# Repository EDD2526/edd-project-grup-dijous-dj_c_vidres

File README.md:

View this project on [CADLAB.io](https://cadlab.io/project/30197).

# Projecte DJ_C_Vidres (Portes)

> **Autors: Gurpinder Singh Kaur, Adria Pelegri Sabate**  
> **Versió: 5**

---

## Objectiu

PCB per al control d’un sistema de porta i alçavidres d’un vehicle. La placa permet controlar el moviment del vidre i l’actuació de la porta mitjançant botons, gestionar motors amb drivers pont H, detectar finals de carrera i situacions de sobrecorrent, i comunicar-se amb altres sistemes del vehicle mitjançant CAN. També inclou mecanismes de protecció, regulació d’alimentació, programació/debug mitjançant ICSP i test points per facilitar la depuració.

---

## Diagrama de blocs

---

## Descripció funcional dels blocs

### Alimentació

La placa s’alimenta a partir d’una entrada de 12 V del vehicle. Aquesta entrada està protegida mitjançant fusible, díode de protecció i TVS. A partir d’aquesta tensió es genera una línia de 5 V mitjançant un convertidor DC-DC LM2596S-5.0. Posteriorment, es genera una línia de 3.3 V mitjançant un regulador LM1117-3.3 per alimentar la lògica digital, el microcontrolador, el transceptor CAN i els perifèrics de baixa tensió.

### Microcontrolador

El sistema està controlat per un microcontrolador **PIC24HJ128GP504-I/PT** alimentat a 3.3 V. Aquest dispositiu gestiona les entrades de botons i sensors, genera les ordres de control dels drivers de motor, llegeix el senyal analògic de corrent, comunica amb el lector RFID i permet la comunicació amb altres sistemes mitjançant CAN.

La placa inclou connector de programació/debug ICSP amb les línies MCLR, PGEC i PGED.

### Drivers de motor

S’utilitzen dos drivers **VNH5019A-E** en configuració de pont H:

- Un driver per al motor  de l’alçavidres;
- Un driver per al motor actuador de la porta.

Cada driver permet controlar el motor en ambdós sentits mitjançant senyals digitals INA, INB i PWM.

### Mesura de corrent i antiatrapament

La mesura de corrent es realitza mitjançant la sortida de current sense del driver VNH5019A-E. Aquest senyal s’envia a una entrada ADC del microcontrolador per detectar situacions de sobrecorrent. Aquesta informació permet implementar una funció  tipus antiatrapament en el motor de l’alçavidres.

### Inputs d’usuari i sensors

La placa incorpora entrades per a:

- Botons de pujada i baixada de l’alçavidres
- Control de bloqueig/desbloqueig de porta
- Sensor de final de carrera

Les entrades digitals es connecten al microcontrolador mitjançant resistències de pull-up/pull-down segons la funcionalitat requerida.

### RFID

El sistema inclou connexió per a un lector RFID RC522. Aquest mòdul permet identificar l’usuari o autoritzar accions del sistema. La comunicació amb el microcontrolador es realitza mitjançant SPI.

### Comunicació CAN

La comunicació amb altres sistemes del vehicle es realitza mitjançant un transceptor **SN65HVD230**. El bus CAN disposa de les línies CANH i CANL.

---

## Requisits / Especificacions

### Alimentació

- Entrada principal: 12 V
- Sortida intermèdia: 5 V
- Alimentació lògica: 3.3 V
- Protecció d’entrada mitjançant fusible, díode i TVS

### Microcontrolador

- Model: PIC24HJ128GP504-I/PT
- Encapsulat: TQFP-44
- Alimentació: 3.3 V
- Programació/debug: ICSP
- Perifèrics utilitzats:
  - PWM per al control dels motors
  - ADC per a la lectura de corrent
  - SPI per al lector RFID
  - CAN per a la comunicació amb el vehicle
  - GPIO per a botons, sensors i diagnòstic

### Motors

- Motor alçavidres:
  - Alimentació: 12 V
  - Corrent màxim estimat: fins a 3 A

- Motor actuador de porta:
  - Alimentació: 12 V
  - Control bidireccional mitjançant pont H
  - Control PWM

### Funcionalitats principals

- Control bidireccional dels motors
- Control de velocitat mitjançant PWM
- Lectura de botons d’usuari
- Lectura de final de carrera
- Detecció de sobrecorrent
- Diagnòstic dels drivers de motor
- Comunicació CAN
- Connexió RFID
- Programació i debug mitjançant ICSP
- Test point per depuració

---

## Components principals

| # | Component | Valor | Quantitat | Footprint | Preu x1 (€) |
|---|---|---|---|---|---|
| 1 | Capacitor | 100nF | 12 | Capacitor_SMD:C_0805_2012Metric | 0,09 |
| 2 | Capacitor | 10uF | 6 | Capacitor_SMD:C_0805_2012Metric | 0,79 |
| 3 | Capacitor | 220uF | 1 | Capacitor_SMD:CP_Elec_8x10 | 0,46 |
| 4 | Capacitor | 22pF | 2 | Capacitor_SMD:C_0805_2012Metric | 0,67 |
| 5 | Capacitor | 100uF | 1 | Capacitor_SMD:CP_Elec_8x10 | 0,69 |
| 6 | Diode Schottky | - | 2 | Diode_SMD:D_SMB_Modified | 0,22 |
| 7 | Diode TVS | - | 1 | Diode_SMD:D_SMB_Modified | 0,66 |
| 8 | Fuse | - | 1 | Fuse:Fuse_1812_4532Metric | 0,45 |
| 9 | Connector | - | 2 | Connector_Dsub:DSUB-9_Pins_Horizontal_P2.77x2.84mm_EdgePinOffset4.9 | 3,89 |
| 10 | Connector | - | 1 | Connector_PinSocket_1.00mm:PinSocket_1x08_P1.00mm_Vertical | 0,80 |
| 11 | Connector | - | 1 | Connector_PinHeader_2.54mm:PinHeader_1x05_P2.54mm_Vertical | 0,24 |
| 12 | Connector | - | 4 | TerminalBlock:TerminalBlock_MaiXu_MX126-5.0-02P_1x02_P5.00mm | 0,09 |
| 13 | Inductor | 33uH | 1 | Inductor_SMD:L_10.4x10.4_H4.8 | 1,38 |
| 14 | Resistor | 120Ω | 1 | Resistor_SMD:R_0805_2012Metric | 1,08 |
| 15 | Resistor | 10kΩ | 10 | Resistor_SMD:R_0805_2012Metric | 1,08 |
| 16 | Resistor | 1kΩ | 1 | Resistor_SMD:R_0805_2012Metric | 1,08 |
| 17 | Switch | - | 1 | Button_Switch_SMD:SW_DPDT_CK_JS202011JCQN | 0,86 |
| 18 | Switch | - | 1 | Button_Switch_THT:SW_CK_JS202011CQN_DPDT_Straight | 0,74 |
| 19 | Switch | - | 1 | Button_Switch_SMD:SW_SPST_TL3342 | 0,50 |
| 20 | Micro | - | 1 | PIC24HJ128GP504-I_PT:QFP80P1200X1200X120-44N | 7,23 |
| 21 | Transceiver | - | 1 | PACKAGE_SO:SOIC-8_3.9x4.9mm_P1.27mm | 1,87 |
| 22 | Motor Drivers | - | 2 | Package_SO:ST_MultiPowerSO-30 | 7,93 |
| 23 | DC-DC | - | 1 | Package_TO_SOT_SMD:TO-263-5_TabPin3 | 5,99 |
| 24 | DC-DC | - | 1 | Package_TO_SOT_SMD:TO-252-3_TabPin2 | 1,12 |
| 25 | Crystal | 8MHz | 1 | Crystal:Crystal_SMD_3225-4Pin_3.2x2.5mm | 0,53 |

## Disseny PCB

La PCB s’ha dissenyat a **dues capes**. S’ha intentat separar funcionalment la zona de potència i la zona lògica per reduir interferències i facilitar el routing.

### Criteris principals de disseny

- Zona de potència situada principalment a l’esquerra de la PCB.
- Microcontrolador situat a la zona central.
- Comunicacions CAN i connectors principals situats a la dreta.
- Inputs i botons situats a la zona inferior/superior.
- Pla de VBAT_PROT per alimentar els drivers de motor.
- Pla de +3.3V per alimentar la part digital.
- Separació entre GND i GNDPWR
- Pistes de potència més amples que les pistes de senyal.
- Test points  per a alimentació, debug, CAN, PWM, diagnòstic i corrent.

### Bus CAN

El transceptor CAN s’ha col·locat pròxim al connector corresponent. Les línies `CANH` i `CANL` s’han mantingut curtes i amb una disposició simètrica.

---

## Test points

S’han afegit test points per facilitar la posada en marxa i la depuració de la placa. Els punts principals són:

- TP_VBAT: alimentació protegida de 12 V
- TP_5V: sortida del convertidor DC-DC
- TP_3V3: alimentació lògica
- TP_GND: massa lògica
- TP_GNDPWR: massa de potència
- TP_MCLR: reset/programació
- TP_PGEC: línia de clock ICSP
- TP_PGED: línia de dades ICSP
- TP_CANH: línia CANH
- TP_CANL: línia CANL
- TP_CURRENT: lectura de corrent
- TP_PWM: control PWM
- TP_WDIAG: diagnòstic del driver de finestra
- TP_DDIAG: diagnòstic del driver de porta

Aquests punts permeten verificar alimentació, comunicació, programació, control dels motors i diagnòstic sense modificar la placa.

---

## Software

### Eines utilitzades

- KiCad 9.0
- LTspice per a simulacions

### Configuració prevista del microcontrolador

- PWM per al control dels drivers de motor
- ADC per a lectura del senyal de corrent
- SPI per al lector RFID
- CAN per a comunicació amb el vehicle
- GPIO per a botons, sensors, finals de carrera i diagnòstic
- ICSP per a programació i debug

### Funcionalitats previstes

#### Control de motors

- Control de pujada i baixada del vidre
- Control d’actuació de la porta
- Control de velocitat mitjançant PWM
- Control de sentit mitjançant INA i INB

#### Seguretat

- Detecció de sobrecorrent
- Funció antiatrapament
- Lectura de final de carrera
- Diagnòstic dels drivers de motor

#### Comunicació

- Comunicació CAN amb altres sistemes del vehicle
- Comunicació SPI amb el lector RFID

#### Debug

- Programació mitjançant ICSP
- Test points per a mesures elèctriques

---

## Verificació

Abans de la fabricació/entrega s’han revisat els punts següents:

- ERC del circuit esquemàtic:
  - 0 errors
  - 6 avisos 
- DRC de la PCB:
  - 0 errors
  - 0 avisos
- Separació entre zona de potència i zona lògica.
- Bus CAN curt i simètric.
- Serigrafia completa i llegible.
- Test points accessibles.

---

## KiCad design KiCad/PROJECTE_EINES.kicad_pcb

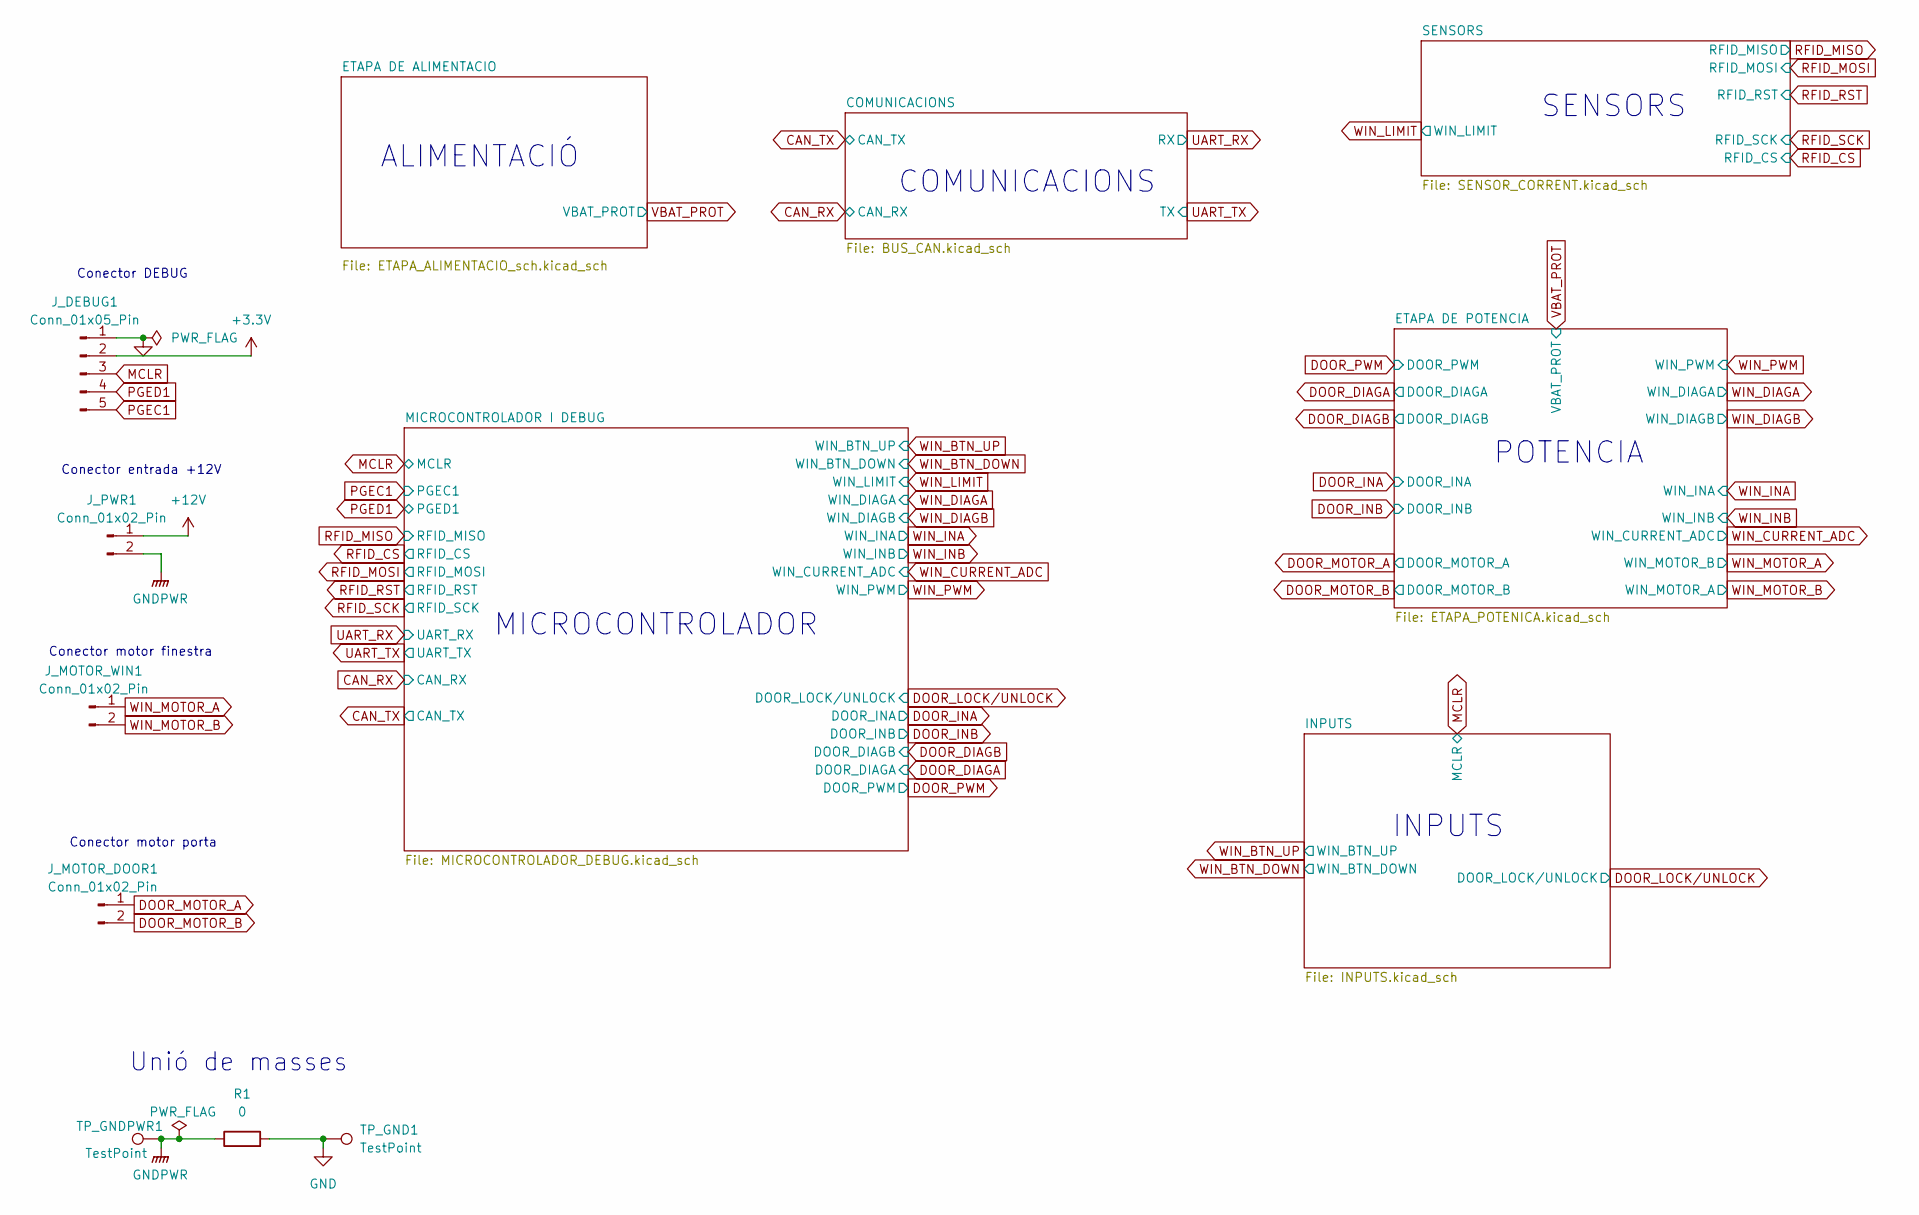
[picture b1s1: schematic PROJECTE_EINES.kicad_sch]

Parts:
J_DEBUG1: Conn_01x05_Pin; PinHeader_1x05_P2.54mm_Vertical
J_MOTOR_DOOR1: Conn_01x02_Pin; TerminalBlock_MaiXu_MX126-5.0-02P_1x02_P5.00mm
J_MOTOR_WIN1: Conn_01x02_Pin; TerminalBlock_MaiXu_MX126-5.0-02P_1x02_P5.00mm
J_PWR1: Conn_01x02_Pin; TerminalBlock_MaiXu_MX126-5.0-02P_1x02_P5.00mm
R1: 0; R_0805_2012Metric
TP_GND1: TestPoint; TestPoint_Pad_D1.5mm
TP_GNDPWR1: TestPoint; TestPoint_Pad_D1.5mm

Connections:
+3.3V: J_DEBUG1.2; also elsewhere on the board
+12V: J_PWR1.1; also elsewhere on the board
DOOR_MOTOR_A: J_MOTOR_DOOR1.1; also elsewhere on the board
DOOR_MOTOR_B: J_MOTOR_DOOR1.2; also elsewhere on the board
GND: J_DEBUG1.1, R1.2, TP_GND1.1; also elsewhere on the board
GNDPWR: J_PWR1.2, R1.1, TP_GNDPWR1.1; also elsewhere on the board
MCLR: J_DEBUG1.3; also elsewhere on the board
PGEC1: J_DEBUG1.5; also elsewhere on the board
PGED1: J_DEBUG1.4; also elsewhere on the board
WIN_MOTOR_A: J_MOTOR_WIN1.1; also elsewhere on the board
WIN_MOTOR_B: J_MOTOR_WIN1.2; also elsewhere on the board

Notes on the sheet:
Unió de masses
COMUNICACIONS
POTENCIA
Conector motor finestra
Conector DEBUG
MICROCONTROLADOR
INPUTS
Conector motor porta
ALIMENTACIÓ
Conector entrada +12V
SENSORS

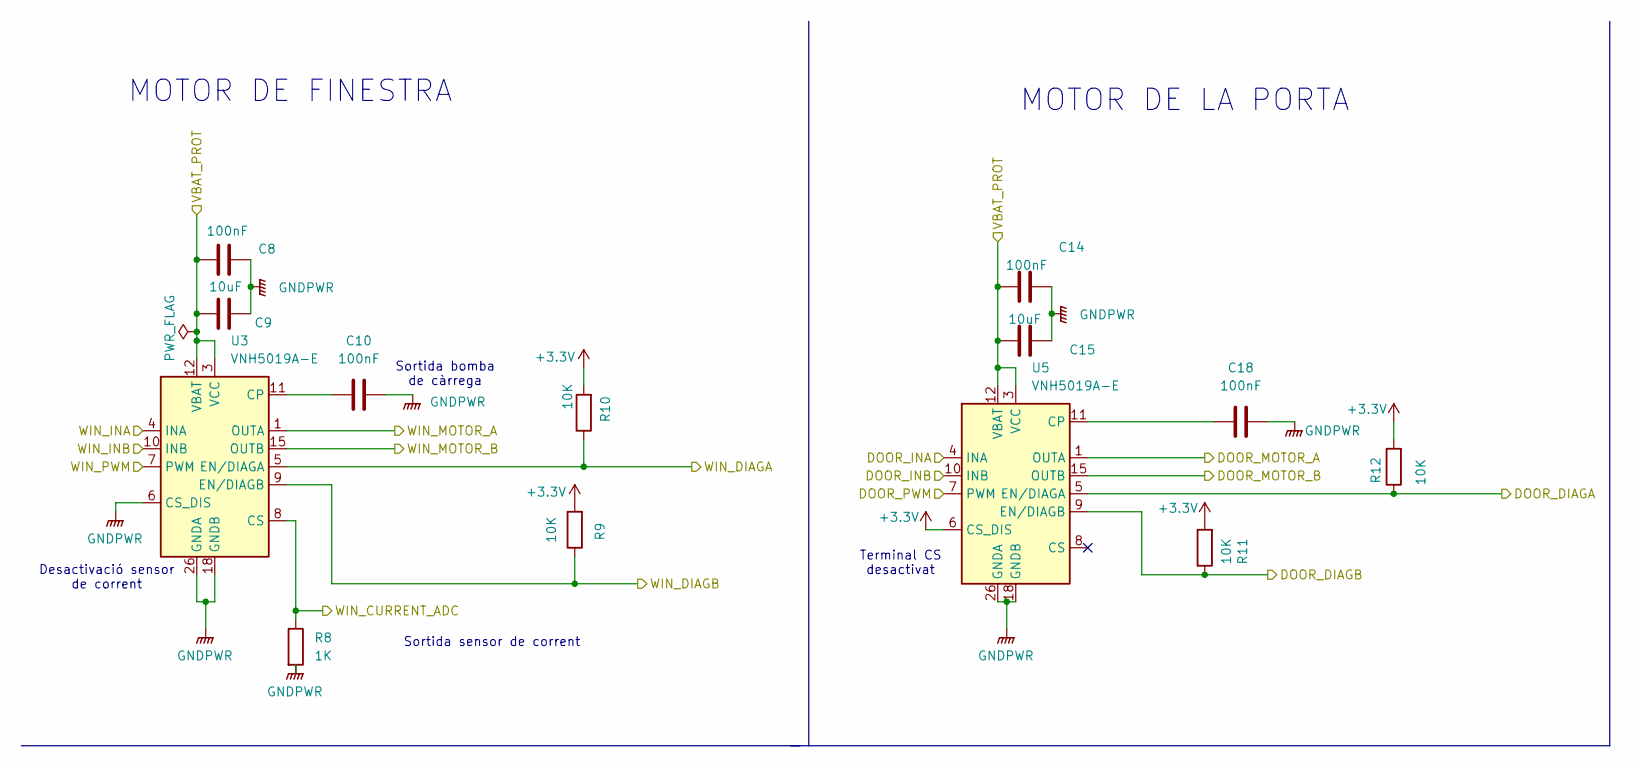
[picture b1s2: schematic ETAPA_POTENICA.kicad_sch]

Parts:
C8, C10, C14, C18: 100nF; C_0805_2012Metric
C9, C15: 10uF; C_1206_3216Metric
R8: 1K; R_0805_2012Metric
R9, R10, R11, R12: 10K; R_0805_2012Metric
U3, U5: VNH5019A-E; ST_MultiPowerSO-30

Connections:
+3.3V: R9.2, R10.2, R11.2, R12.2, U5.6 (CS_DIS); also elsewhere on the board
DOOR_DIAGA: R12.1, U5.5 (EN/DIAGA); also elsewhere on the board
DOOR_DIAGB: R11.1, U5.9 (EN/DIAGB); also elsewhere on the board
DOOR_INA: U5.4 (INA); also elsewhere on the board
DOOR_INB: U5.10 (INB); also elsewhere on the board
DOOR_MOTOR_A: U5.1 (OUTA), U5.25 (OUTA), U5.30 (OUTA), U5.33 (OUTA); also elsewhere on the board
DOOR_MOTOR_B: U5.15 (OUTB), U5.16 (OUTB), U5.21 (OUTB), U5.32 (OUTB); also elsewhere on the board
DOOR_PWM: U5.7 (PWM); also elsewhere on the board
GNDPWR: C8.2, C9.2, C10.1, C14.2, C15.2, C18.1, R8.2, U3.6 (CS_DIS), U3.18 (GNDB), U3.19 (GNDB), U3.20 (GNDB), U3.26 (GNDA), U3.27 (GNDA), U3.28 (GNDA), U5.18 (GNDB), U5.19 (GNDB), U5.20 (GNDB), U5.26 (GNDA), U5.27 (GNDA), U5.28 (GNDA); also elsewhere on the board
unnamed: C10.2, U3.11 (CP)
unnamed: C18.2, U5.11 (CP)
VBAT_PROT: C8.1, C9.1, C14.1, C15.1, U3.3 (VCC), U3.12 (VBAT), U3.13 (VCC), U3.23 (VCC), U3.31 (VCC), U5.3 (VCC), U5.12 (VBAT), U5.13 (VCC), U5.23 (VCC), U5.31 (VCC); also elsewhere on the board
WIN_CURRENT_ADC: R8.1, U3.8 (CS); also elsewhere on the board
WIN_DIAGA: R10.1, U3.5 (EN/DIAGA); also elsewhere on the board
WIN_DIAGB: R9.1, U3.9 (EN/DIAGB); also elsewhere on the board
WIN_INA: U3.4 (INA); also elsewhere on the board
WIN_INB: U3.10 (INB); also elsewhere on the board
WIN_MOTOR_A: U3.15 (OUTB), U3.16 (OUTB), U3.21 (OUTB), U3.32 (OUTB); also elsewhere on the board
WIN_MOTOR_B: U3.1 (OUTA), U3.25 (OUTA), U3.30 (OUTA), U3.33 (OUTA); also elsewhere on the board
WIN_PWM: U3.7 (PWM); also elsewhere on the board

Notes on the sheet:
Sortida bomba de càrrega
MOTOR DE FINESTRA
MOTOR DE LA PORTA
Desactivació sensor de corrent
Terminal CS desactivat
Sortida sensor de corrent

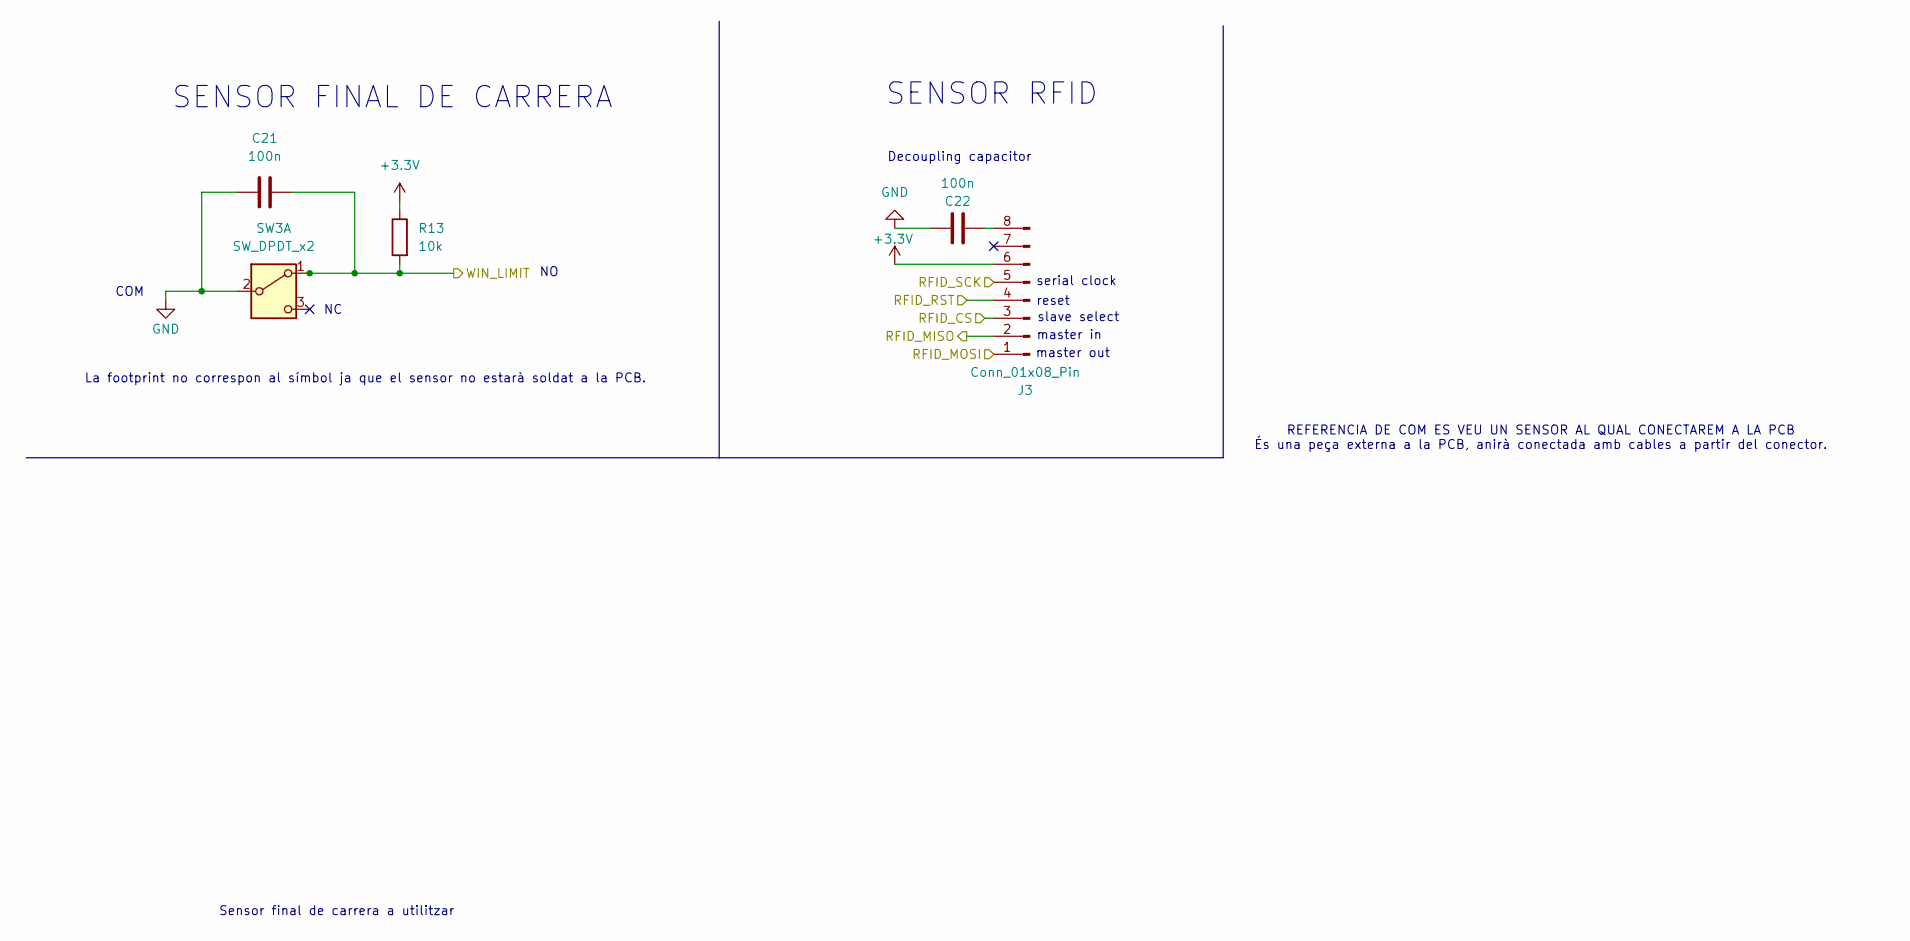
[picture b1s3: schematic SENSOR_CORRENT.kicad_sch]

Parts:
C21, C22: 100n; C_0805_2012Metric
J3: Conn_01x08_Pin; PinSocket_1x08_P1.00mm_Vertical
R13: 10k; R_0805_2012Metric
SW3: SW_DPDT_x2; TerminalBlock_MaiXu_MX126-5.0-02P_1x02_P5.00mm

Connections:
+3.3V: J3.6 (GND), R13.1; also elsewhere on the board
GND: C21.1, C22.2, SW3.2 (B); also elsewhere on the board
unnamed: C22.1, J3.8 (3.3V)
RFID_CS: J3.3 (MOSI); also elsewhere on the board
RFID_MISO: J3.2 (SCK); also elsewhere on the board
RFID_MOSI: J3.1 (SDA); also elsewhere on the board
RFID_RST: J3.4 (MISO); also elsewhere on the board
RFID_SCK: J3.5 (IRQ); also elsewhere on the board
WIN_LIMIT: C21.2, R13.2, SW3.1 (A); also elsewhere on the board

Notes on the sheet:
La footprint no correspon al símbol ja que el sensor no estarà soldat a la PCB.
Decoupling capacitor
serial clock
COM
slave select
SENSOR RFID
REFERENCIA DE COM ES VEU UN SENSOR AL QUAL CONECTAREM A LA PCB És una peça externa a la PCB, anirà conectada amb cables a partir del conector.
Sensor final de carrera a utilitzar
master in
reset
SENSOR FINAL DE CARRERA
master out

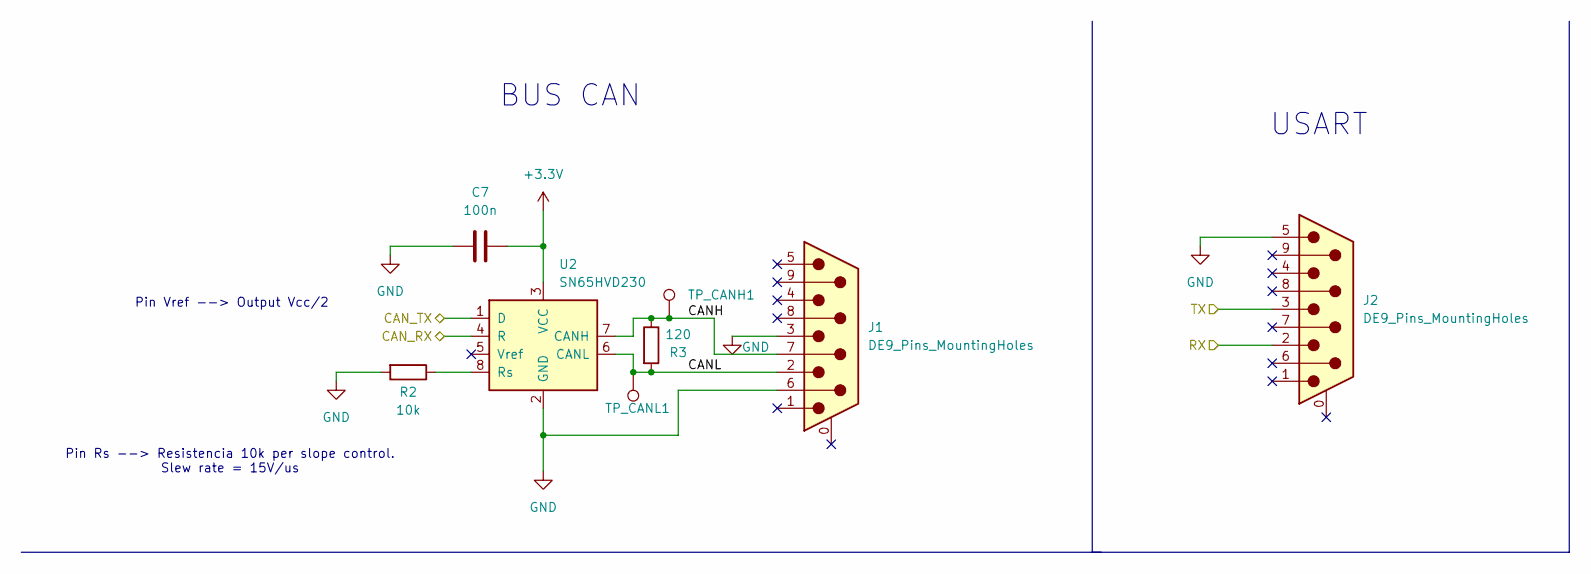
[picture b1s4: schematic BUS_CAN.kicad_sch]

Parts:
C7: 100n; C_0805_2012Metric
J1, J2: DE9_Pins_MountingHoles; DSUB-9_Pins_Horizontal_P2.77x2.84mm_EdgePinOffset4.94mm_Hou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
R2: 10k; R_0805_2012Metric
R3: 120; R_0805_2012Metric
TP_CANH1: TestPoint_Pad_D1.5mm
TP_CANL1: TestPoint_Pad_D1.5mm
U2: SN65HVD230; SOIC-8_3.9x4.9mm_P1.27mm

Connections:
+3.3V: C7.2, U2.3 (VCC); also elsewhere on the board
/COMUNICACIONS/CANH: J1.7, R3.1, TP_CANH1.1, U2.7 (CANH)
/COMUNICACIONS/CANL: J1.2, R3.2, TP_CANL1.1, U2.6 (CANL)
CAN_RX: U2.4 (R); also elsewhere on the board
CAN_TX: U2.1 (D); also elsewhere on the board
GND: C7.1, J1.3, J1.6, J2.5, R2.2, U2.2 (GND); also elsewhere on the board
unnamed: R2.1, U2.8 (Rs)
UART_RX: J2.2; also elsewhere on the board
UART_TX: J2.3; also elsewhere on the board

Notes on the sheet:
USART
Pin Vref --> Output Vcc/2
Pin Rs --> Resistencia 10k per slope control. Slew rate = 15V/us
BUS CAN

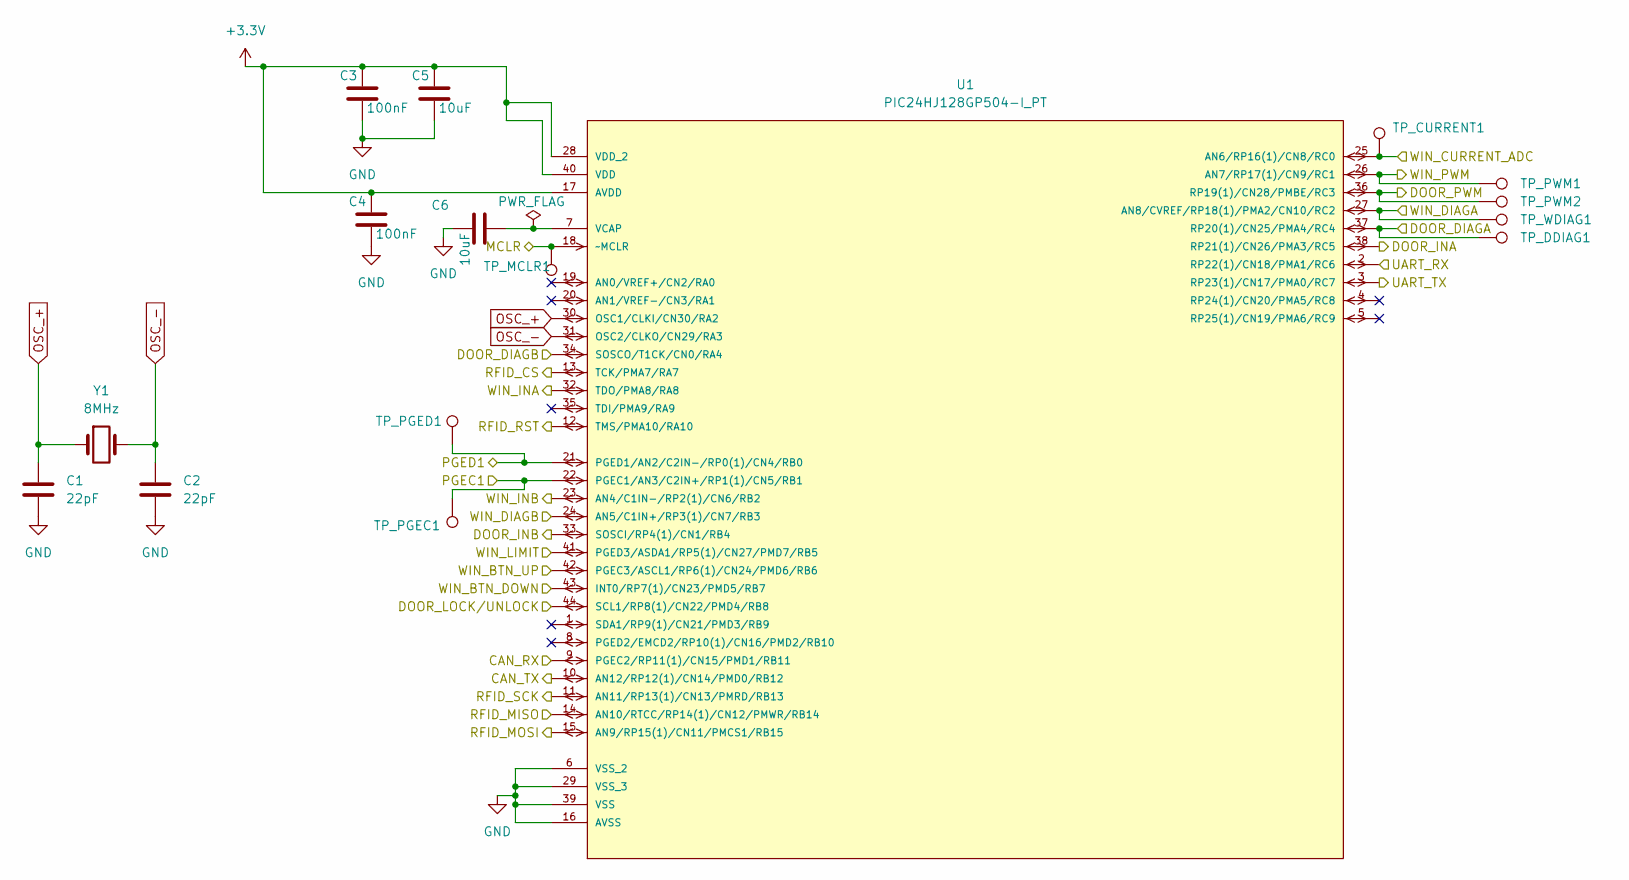
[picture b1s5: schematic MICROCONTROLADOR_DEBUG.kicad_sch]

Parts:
C1, C2: 22pF; C_0603_1608Metric
C3, C4: 100nF; C_0805_2012Metric
C5, C6: 10uF; C_0805_2012Metric
TP_CURRENT1: TestPoint_Pad_D1.5mm
TP_DDIAG1: TestPoint_Pad_D1.5mm
TP_MCLR1: TestPoint_Pad_D1.5mm
TP_PGEC1: TestPoint_Pad_D1.5mm
TP_PGED1: TestPoint_Pad_D1.5mm
TP_PWM1, TP_PWM2: TestPoint_Pad_D1.5mm
TP_WDIAG1: TestPoint_Pad_D1.5mm
U1: PIC24HJ128GP504-I_PT; QFP80P1200X1200X120-44N; MPN PIC24HJ128GP504-I/PT
Y1: 8MHz; Crystal_SMD_3225-4Pin_3.2x2.5mm

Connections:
+3.3V: C3.1, C4.1, C5.1, U1.17 (AVDD), U1.28 (VDD_2), U1.40 (VDD); also elsewhere on the board
CAN_RX: U1.9 (PGEC2/RP11(1)/CN15/PMD1/RB11); also elsewhere on the board
CAN_TX: U1.10 (AN12/RP12(1)/CN14/PMD0/RB12); also elsewhere on the board
DOOR_DIAGA: TP_DDIAG1.1, U1.37 (RP20(1)/CN25/PMA4/RC4); also elsewhere on the board
DOOR_DIAGB: U1.34 (SOSCO/T1CK/CN0/RA4); also elsewhere on the board
DOOR_INA: U1.38 (RP21(1)/CN26/PMA3/RC5); also elsewhere on the board
DOOR_INB: U1.33 (SOSCI/RP4(1)/CN1/RB4); also elsewhere on the board
DOOR_LOCK/UNLOCK: U1.44 (SCL1/RP8(1)/CN22/PMD4/RB8); also elsewhere on the board
DOOR_PWM: TP_PWM2.1, U1.36 (RP19(1)/CN28/PMBE/RC3); also elsewhere on the board
GND: C1.2, C2.2, C3.2, C4.2, C5.2, C6.2, U1.6 (VSS_2), U1.16 (AVSS), U1.29 (VSS_3), U1.39 (VSS); also elsewhere on the board
MCLR: TP_MCLR1.1, U1.18 (~MCLR); also elsewhere on the board
unnamed: C6.1, U1.7 (VCAP)
OSC_+: C1.1, U1.30 (OSC1/CLKI/CN30/RA2), Y1.1
OSC_-: C2.1, U1.31 (OSC2/CLKO/CN29/RA3), Y1.2
PGEC1: TP_PGEC1.1, U1.22 (PGEC1/AN3/C2IN+/RP1(1)/CN5/RB1); also elsewhere on the board
PGED1: TP_PGED1.1, U1.21 (PGED1/AN2/C2IN-/RP0(1)/CN4/RB0); also elsewhere on the board
RFID_CS: U1.13 (TCK/PMA7/RA7); also elsewhere on the board
RFID_MISO: U1.14 (AN10/RTCC/RP14(1)/CN12/PMWR/RB14); also elsewhere on the board
RFID_MOSI: U1.15 (AN9/RP15(1)/CN11/PMCS1/RB15); also elsewhere on the board
RFID_RST: U1.12 (TMS/PMA10/RA10); also elsewhere on the board
RFID_SCK: U1.11 (AN11/RP13(1)/CN13/PMRD/RB13); also elsewhere on the board
UART_RX: U1.2 (RP22(1)/CN18/PMA1/RC6); also elsewhere on the board
UART_TX: U1.3 (RP23(1)/CN17/PMA0/RC7); also elsewhere on the board
WIN_BTN_DOWN: U1.43 (INT0/RP7(1)/CN23/PMD5/RB7); also elsewhere on the board
WIN_BTN_UP: U1.42 (PGEC3/ASCL1/RP6(1)/CN24/PMD6/RB6); also elsewhere on the board
WIN_CURRENT_ADC: TP_CURRENT1.1, U1.25 (AN6/RP16(1)/CN8/RC0); also elsewhere on the board
WIN_DIAGA: TP_WDIAG1.1, U1.27 (AN8/CVREF/RP18(1)/PMA2/CN10/RC2); also elsewhere on the board
WIN_DIAGB: U1.24 (AN5/C1IN+/RP3(1)/CN7/RB3); also elsewhere on the board
WIN_INA: U1.32 (TDO/PMA8/RA8); also elsewhere on the board
WIN_INB: U1.23 (AN4/C1IN-/RP2(1)/CN6/RB2); also elsewhere on the board
WIN_LIMIT: U1.41 (PGED3/ASDA1/RP5(1)/CN27/PMD7/RB5); also elsewhere on the board
WIN_PWM: TP_PWM1.1, U1.26 (AN7/RP17(1)/CN9/RC1); also elsewhere on the board

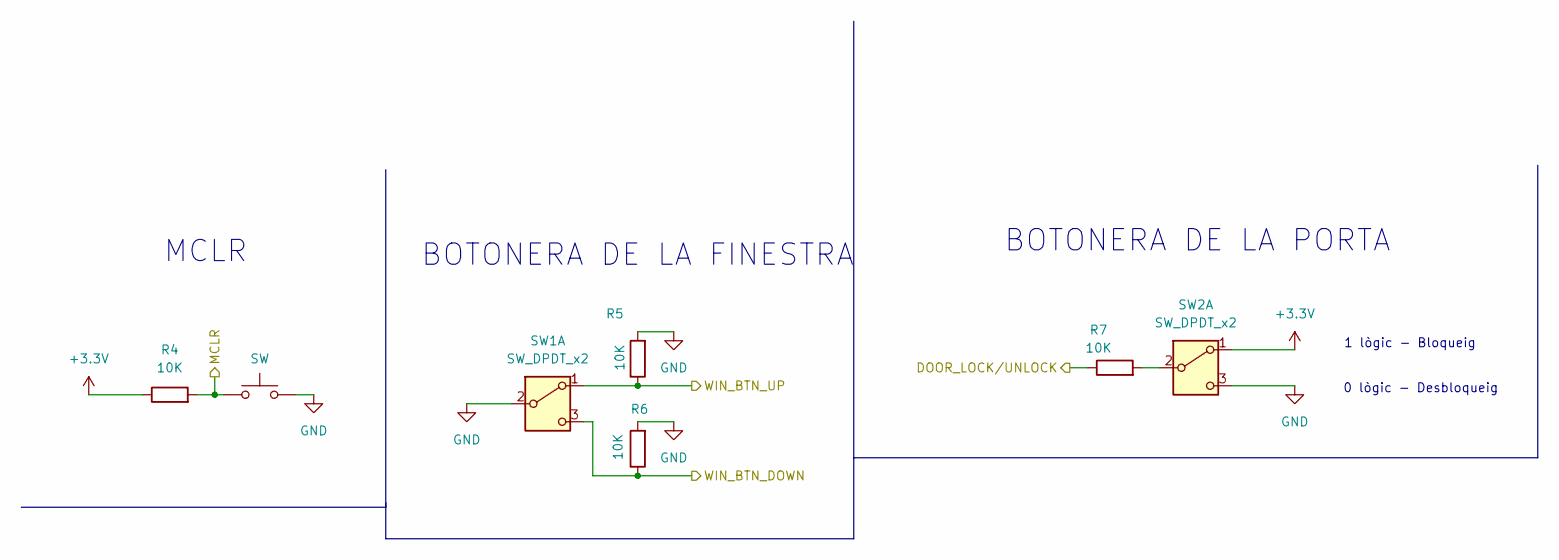
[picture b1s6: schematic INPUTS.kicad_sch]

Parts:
R4, R5, R6, R7: 10K; R_0805_2012Metric
SW1: SW_DPDT_x2; SW_DPDT_CK_JS202011JCQN
SW2: SW_DPDT_x2; SW_CK_JS202011CQN_DPDT_Straight
SW_UP1: SW; SW_SPST_TL3342

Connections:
+3.3V: R4.1, SW2.1 (A); also elsewhere on the board
DOOR_LOCK/UNLOCK: R7.1; also elsewhere on the board
GND: R5.2, R6.2, SW1.2 (B), SW2.3 (C), SW_UP1.2; also elsewhere on the board
MCLR: R4.2, SW_UP1.1; also elsewhere on the board
unnamed: R7.2, SW2.2 (B)
WIN_BTN_DOWN: R6.1, SW1.3 (C); also elsewhere on the board
WIN_BTN_UP: R5.1, SW1.1 (A); also elsewhere on the board

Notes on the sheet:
0 lògic - Desbloqueig
BOTONERA DE LA FINESTRA
1 lògic - Bloqueig
MCLR
BOTONERA DE LA PORTA

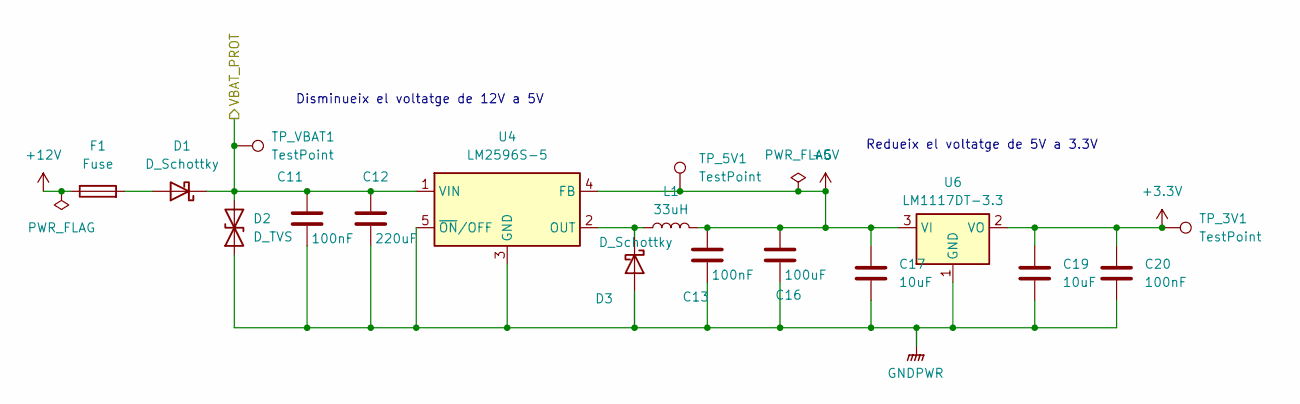
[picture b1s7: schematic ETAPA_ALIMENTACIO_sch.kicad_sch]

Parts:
C11, C13, C20: 100nF; C_0805_2012Metric
C12: 220uF; CP_Elec_8x10
C16: 100uF; CP_Elec_8x10
C17, C19: 10uF; C_1206_3216Metric
D1, D3: D_Schottky; D_SMB_Modified
D2: D_TVS; D_SMB_Modified
F1: Fuse; Fuse_1812_4532Metric
L1: 33uH; L_10.4x10.4_H4.8
TP_3V1, TP_5V1: TestPoint; TestPoint_Pad_D1.5mm
TP_VBAT1: TestPoint; TestPoint_Pad_D1.5mm
U4: LM2596S-5; TO-263-5_TabPin3
U6: LM1117DT-3.3; TO-252-3_TabPin2

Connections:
+3.3V: C19.1, C20.1, TP_3V1.1, U6.2 (VO); also elsewhere on the board
+5V: C13.1, C16.1, C17.1, L1.2, TP_5V1.1, U4.4 (FB), U6.3 (VI)
+12V: F1.1; also elsewhere on the board
GNDPWR: C11.2, C12.2, C13.2, C16.2, C17.2, C19.2, C20.2, D2.1 (A1), D3.2 (A), U4.3 (GND), U4.5 (~ON/OFF), U6.1 (GND); also elsewhere on the board
unnamed: D1.2 (A), F1.2
unnamed: D3.1 (K), L1.1, U4.2 (OUT)
VBAT_PROT: C11.1, C12.1, D1.1 (K), D2.2 (A2), TP_VBAT1.1, U4.1 (VIN); also elsewhere on the board

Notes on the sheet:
Disminueix el voltatge de 12V a 5V
Redueix el voltatge de 5V a 3.3V

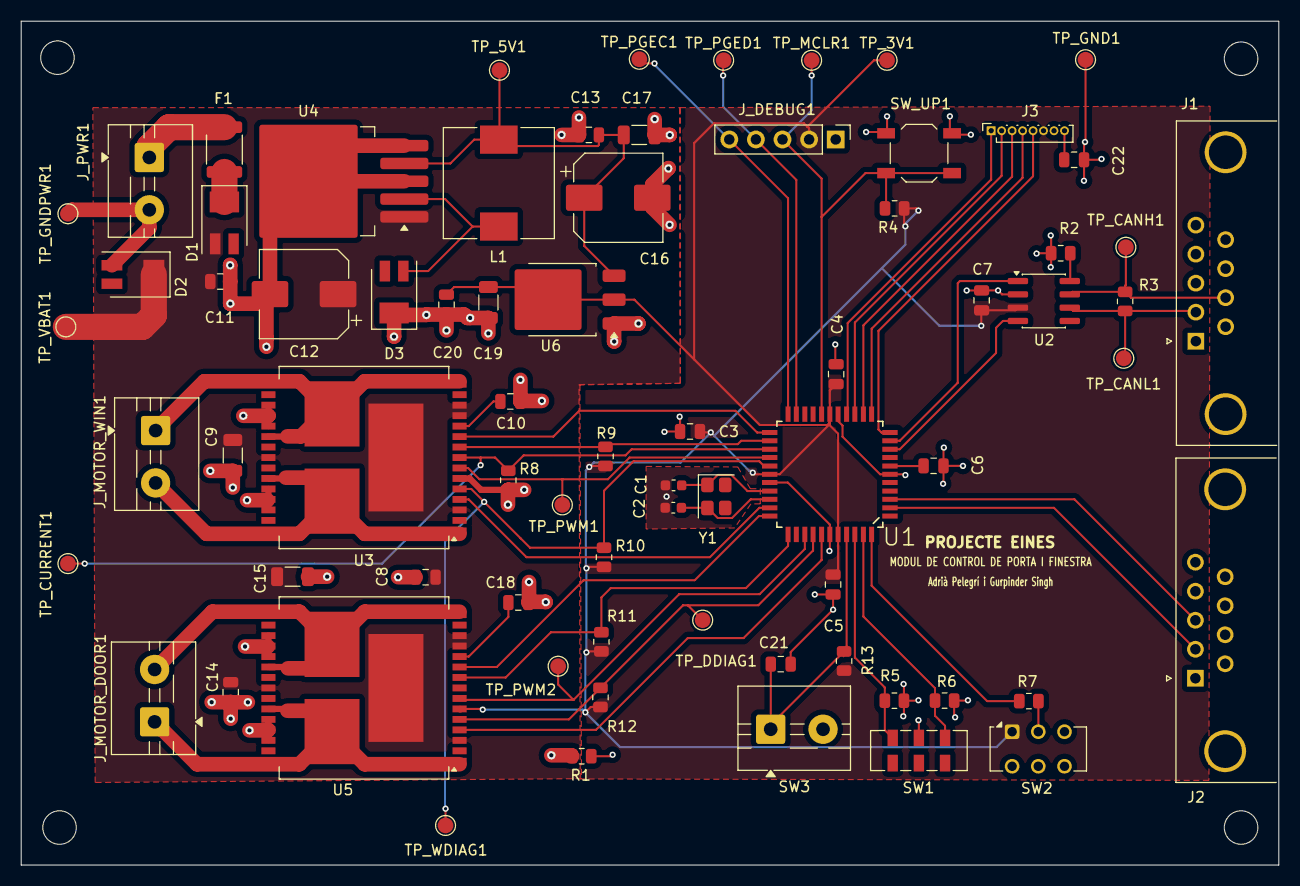
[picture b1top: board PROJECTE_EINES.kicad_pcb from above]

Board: 2 copper layers, 120.1 x 80.6 mm, 73 parts (0 on the bottom side), 49 nets.

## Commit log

2026-03-12 ACTUALITZACIÓ README
2026-03-12 CREACIÓ PROJECTE
2026-03-12 Pujada d'esquematic inicial
2026-03-16 Backlink to CADLAB.io has been added.
2026-03-18 Nova versió diagrama de blocs i primera versió BOM
2026-03-19 CREACIÓ DE BLOCS DEL PROJECTE
2026-03-19 Actualització del sensor de corrent
2026-03-19 Versió amb el simbol del nou micro
2026-03-19 Esquematic BUS creat + Diagrama blocs v.3.
2026-03-19 aclaracions BUS CAN
2026-03-19 Update del micro
2026-03-19 BUS CAN + USART +GND comuns
2026-03-25 Diagrama blocs versió 4 + BOM actualitzat + Bus CAN i USART + Lector RFID
2026-03-25 Footprints afegides a Comunicació, Sensor RFID i Sensor Corrent
2026-03-26 Actualizació final de les conexions del microcontrolador
2026-03-26 Actulització del driver del motor de finestra
2026-03-26 Actulització etapa d'alimentació
2026-03-26 Actualització Sheet Inputs
2026-03-26 Esquematic general conectat
2026-03-26 ESQUEMATIC FINAL V.1
2026-03-26 Nova versió diagrama de blocs + BOM actualitzat + Nova versió KiCad
2026-03-26 Resistències pull-up arreglades als motors
2026-03-26 Etiquetes de GND i VCC 3.3V canviades a simbols
2026-03-27 Eliminat .sch inecessari del projecte KiCad
2026-04-06 Correció etapa d'alimentació e Inputs
2026-04-07 Actualizació Footprints
2026-04-08 Update del nou Microcontrolador
2026-04-08 Versió final Esquematic
2026-04-09 Versió final de l'esquematic
2026-04-09 1ra versióPCB
2026-04-09 Versió 2.0 PCB
2026-04-09 Versió de placement PCB
2026-04-15 Inputs
2026-04-15 Actulitació de components
2026-04-15 Bus CAN i USART
2026-04-15 Recover
2026-04-15 Errors solucionats
2026-04-15 V3 layout
2026-04-15 Update pels dos
2026-04-15 V2 placement
2026-04-15 REORDENACIÓ DEL MICRO
2026-04-16 V1 Routing
2026-04-16 V2 Routing
2026-04-16 Update dels testpins
2026-04-16 Routing V3
2026-04-29 Versió preliminar Routing Final
2026-04-29 Actualització dels test points
2026-04-29 Versio final KiCad, BOM i Diagrama de Blocs
2026-04-29 BOM + Diagrama
2026-04-29 Afegida foodprint a R4 i actualitzada a la PCB
2026-04-30 Versio final
2026-04-30 Versió Final projecte
2026-04-30 Presupost afegit, readme actualitzat, diagrama de blocs jpg
2026-04-30 Entrega final de projecte
2026-04-30 Final Read.me
